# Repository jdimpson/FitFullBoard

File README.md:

FitFullBoard is a Raspberry Pi- and Raspberry Pi Zero-compatible daughter board intended to power up and power down the the RPi board in sync with outside signals. 

I use it to keep an RPi media player powered along with my television. I connect the fitfullboard's signal pin called EXTERNAL to a USB cable which I plug into my smart teevee (but I power the RPi from an independent power source.) When the teevee comes on, it brings its USB port on, which wakes up the RPi. When the teevee goes off, it brings its USB port down, which puts the RPi to sleep (following a configurable grace period).  It is possible to turn the teevee back on at just the wrong time so as to get them out of sync (after the grace period expires, while the RPi operating system is still shutting down). 

Python software is available in the [RPiIoT](https://github.com/jdimpson/RPiIoT) repo.

FitFullBoard uses an ATtiny85 to control power up / power down and to monitor the EXTERNAL signal, and python code running in the RPi to handle shutdown and grace period. The grace period works because the ATtiny will hold the shutdown signal to the RPI down indefinitely. If the EXTERNAL signal comes back on, the ATtiny with bring the shutdown signal back high again. If this happens within the grace period, the python software will not initiate shutdown. You can instead use the Linux kernel's builtin signal handling for shutdown, althuogh AFAIK it has no way of offering a grace period.

Raspberry Pi Pins used:
- GPIO3/Phys5/SCL is used to power up the RPi. This only works if the RPi has been shut down via the "poweroff" or "shutdown" Linux commands. THe board itself must still have power.
- GPIO17/Phy11 is connected to a momentary / tactile switch. Available for arbitrary software control (typically running my powerboard.py and associated code).
- GPIO27/Phy13 is connected to a resistor and then an LED. Available for arbitrary software control (e.g. flashing to show grace period, and typically running my powerboard.py and associated code).
- GPIO26/Phy37 is connected via transistor and appropriate hold up resistor to the LBO/Shutdown pin of the ATtiny85. This is how the Raspberry Pi knows to shut down. This is labelled LBO and referred to as "Low Battery" in the schematic because the circuit and my python lowbattery code were reused from the PowerBoard (https://github.com/jdimpson/PowerBoard) and PowerHolder (https://github.com/jdimpson/PowerHolder) projects, in which when the Li Ion battery level fell below 3.4VDC (or whatever) the boards sent an LBO signal to the raspberry pi to shutdown, again with a grace period that allowed you to maybe plug it into external power (typically running my powerboard.py and associated code).

ATtiny85 pin used:
- PB0/MOSI used as RX for soft UART (for debugging, note the arduino code doesn't RX currently)
- PB1/MISO used as TX for soft UART (for debugging)
- PB2/SCK used to send the LBO/shutdown signal that tells the RPi to power off following a grace period.
- PB3 used to receive EXTERNAL signal (e.g. teevee power on indication). Circuit can be held up to 5VDC or down to ground, depending on which pads you put the resistor on (DON'T ATTACH BOTH R4 and R5 RESISTORS).
- PB4 is attached to a momentary / tactile button to allow manual start of the RPi independent of the EXTernal signal.

Other items of Note:
- I honestly don't remember why I called this the FitFullBoard. Something about the phrase "sleeping in fits and starts" being an analogue to automatically starting up and shutting down in response to an external influence. But honestly who knows? At one point I called it GraceFullBoard because it allowed for graceful shutdown of a raspberry pi in response to a signal. I should have kept that name.
- ATtiny85 code works with Arduino IDE and requires the https://github.com/SpenceKonde/ATTinyCore library.
- Python code referenced above will be posted and linked to soon.
- The use of GPIO3 to cause a shutdown RPi to restart does not seem to be well known. At least, it's not referenced on pinout.xyz (https://pinout.xyz/pinout/pin5_gpio3#). I've personally tested it to work on RPi Zero Ws, RPi 3B, and an RPi 4B with updated firmware. Note that this behaviour of GPIO3 is *different* from that of the RUN pin that is found in elsewhere on the board (not on the 40-pin header). The RUN pin will, when brought high, cause the RPi to reboot, even if the CPU is already running. This crashes the OS, which isn't something I want to do regularly. GPIO3 acts like any other pin when the CPU is running normally. It only seems to have special behaviour when the the CPU has halted following a graceful shutdown of the OS. When it gets brought high, it will cause a reboot. But *only* when the CPU was halted. See also https://www.raspberrypi.org/forums/viewtopic.php?t=113200 and https://www.raspberrypi.org/forums/viewtopic.php?p=767687#p767687

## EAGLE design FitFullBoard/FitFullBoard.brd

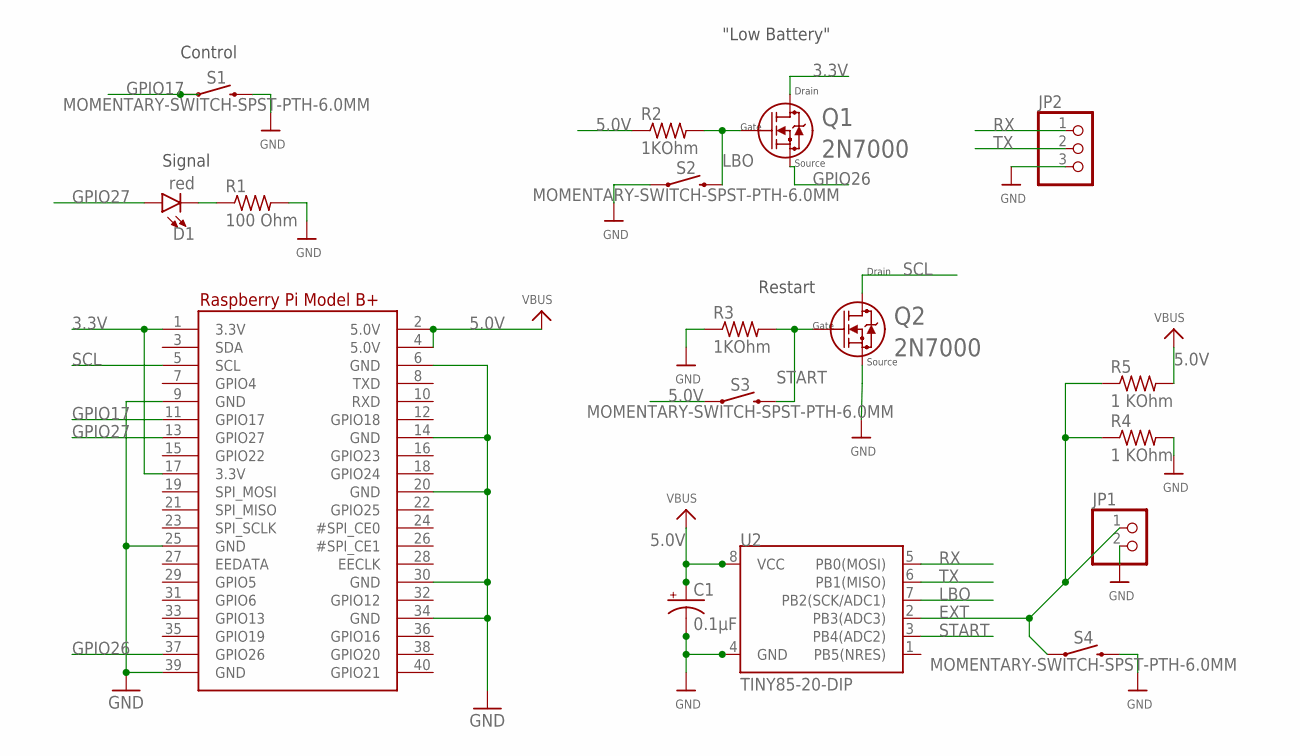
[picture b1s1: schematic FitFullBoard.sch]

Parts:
C1: 0.1µF; E2,5RE
D1: red; LED_5MM
JP1: HEADER-1X2; 1X02_OVAL
JP2: PINHD-1X3CB; 1X03-CLEANBIG
Q1, Q2: 2N7000; TO-92
R1: 100 Ohm; 0805-THM
R2, R3: 1KOhm; 0805-THM
R4, R5: 1 KOhm; 0805-THM
RPI1: RASPBERRYPI_BPLUS_BONNETNODIM; PI_BONNET_NODIM
S1, S2, S3, S4: MOMENTARY-SWITCH-SPST-PTH-6.0MM; TACTILE_SWITCH_PTH_6.0MM
U2: TINY85-20-DIP; DIP08_MCU

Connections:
3.3V: Q1.3 (2), RPI1.1 (3.3V), RPI1.17 (3.3V)
5.0V: C1.+, R2.1, R5.2, RPI1.2 (5.0V), RPI1.4 (5.0V), S3.1, U2.8 (VCC)
EXT: JP1.1, R4.1, R5.1, S4.1, U2.2 (PB3(ADC3))
GND: C1.-, JP1.2, JP2.3, Q2.1 (3), R1.2, R3.1, R4.2, RPI1.6 (GND), RPI1.9 (GND), RPI1.14 (GND), RPI1.20 (GND), RPI1.25 (GND), RPI1.30 (GND), RPI1.34 (GND), RPI1.39 (GND), S1.3 (2), S2.1, S4.3 (2), U2.4 (GND)
GPIO17: RPI1.11 (GPIO17), S1.1
GPIO26: Q1.1 (3), RPI1.37 (GPIO26)
GPIO27: D1.A, RPI1.13 (GPIO27)
LBO: Q1.2 (1), R2.2, S2.3 (2), U2.7 (PB2(SCK/ADC1))
unnamed: D1.K (C), R1.1
RX: JP2.1, U2.5 (PB0(MOSI))
SCL: Q2.3 (2), RPI1.5 (SCL)
START: Q2.2 (1), R3.2, S3.3 (2), U2.3 (PB4(ADC2))
TX: JP2.2, U2.6 (PB1(MISO))

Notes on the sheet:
Signal
Control
Source
Gate
"Low Battery"
Drain
Restart

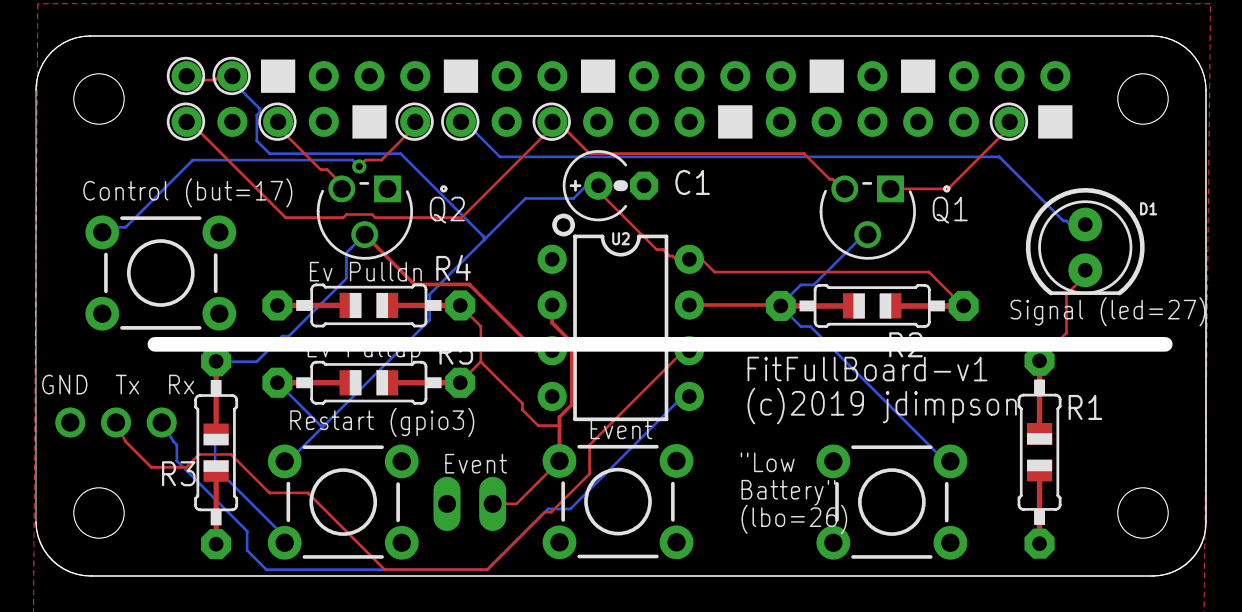
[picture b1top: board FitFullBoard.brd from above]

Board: 2 copper layers, 64.2 x 29.2 mm, 17 parts (0 on the bottom side), 13 nets.

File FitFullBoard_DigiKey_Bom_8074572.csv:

"Manufacturer Part Number","Manufacturer","Digi-Key Part Number","Customer Reference","Reference Designator","Packaging","Part Status","Quantity","Unit Price","Extended Price","Quantity Available","Mfg Std Lead Time","Description","RoHS Status","Lead Free Status","REACH Status"
"ATTINY85-20PU","Microchip Technology","ATTINY85-20PU-ND","U2","","Tube","Active","1","1.20000","$1.20","144","21 Weeks","IC MCU 8BIT 8KB FLASH 8DIP","ROHS3 Compliant","Lead free","REACH Unaffected"
"USP1H0R1MDD","Nichicon","493-15992-ND","C1","","Bulk","Active","1","0.35000","$0.35","2591","15 Weeks","CAP ALUM 0.1UF 20% 50V RADIAL","ROHS3 Compliant","Lead free","REACH Unaffected"
"SFR2500001001FR500","Vishay Beyschlag/Draloric/BC Components","PPC1.00KYCT-ND","R2,R3,R4/5","","Cut Tape (CT)","Active","3","0.14000","$0.42","23724","22 Weeks","RES 1K OHM 0.4W 1% AXIAL","ROHS3 Compliant","Lead free","Not Available"
"SFR2500001000FR500","Vishay Beyschlag/Draloric/BC Components","PPC100YCT-ND","R1","","Cut Tape (CT)","Active","1","0.14000","$0.14","13597","22 Weeks","RES 100 OHM 0.4W 1% AXIAL","ROHS3 Compliant","Lead free","Not Available"
"2N7000-G","Microchip Technology","2N7000-G-ND","Q1,Q2","","Bag","Active","2","0.37000","$0.74","2054","21 Weeks","MOSFET N-CH 60V 0.2A TO92-3","ROHS3 Compliant","Lead free","REACH Unaffected"
"C503B-RAN-CZ0C0AA1","Cree Inc.","C503B-RAN-CZ0C0AA1-ND","D1","","Bulk","Active","1","0.15000","$0.15","51470","4 Weeks","LED RED CLEAR 5MM ROUND T/H","RoHS Compliant","Lead free","Not Available"

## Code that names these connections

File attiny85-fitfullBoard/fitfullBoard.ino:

/**********************************************************************
 * ATTiny85 MCU monitors an external signal. When the signal (EXT) 
 * activates, MCU will bring RPi GPIO3 (START) low, which, if the RPi 
 * previously did a poweroff, will cause it to restart. At the same time, 
 * MCU will bring RPi GPIO26 (LBO) high. When the EXT signal deactivates, 
 * MCU will bring RPi GPIO26 (LBO) low.
 * 
 * The intention for the signal on GPIO26 is that the RPi runs software 
 * that treats it as a low-battery signal. When the software starts up, 
 * it looks at GPIO26. If high, it knows to use the pin as low-battery signal. 
 * (If low, don't monitor pin.) When GPIO26 goes low, RPi software will 
 * initiate a graceful shutdown.
 * 
 * Could probably do both the restart and LBO on GPIO3, but GPIO26 is used
 * for LBO due to commonality with my batter power boards.
 * 
 * Don't forget to level shift the LBO and START pins, assuming MCU is running 
 * at 5V.
 * 
 * (c) 2019 jdimpson
 **********************************************************************/

// NOTE: right now, the EXT signal must be HIGH for on, LOW for off. Would 
// be cool to use EEPROM to store the EXT signal mode, and adjust accordingly.

#include <SoftwareSerial.h>
#include <EEPROM.h>
#include "Debounce.h"

#define EXT   3 // Physical 2 / PB3 / A3
#define START 4 // Physical 3 / PB4
#define RX   -1 // Physical 5 / PB0; Reserved, not currently used. 
#define TX    1 // Physical 6 / PB1
#define LBO   2 // Physical 7 / PB2

#define OFF          0
#define STARTUP      1
#define SYNC_SIGNAL  2
#define HIGH_MONITOR 3
#define LOW_MONITOR  4

SoftwareSerial ss(RX, TX);
Debounce Button(EXT);

int state = STARTUP;
int prevstate = OFF;

void setup() {
  ss.begin(9600);
  ss.println(F("fitfullBoard"));
  ss.println(F(__FILE__));
  ss.print(F("compiled ")); 
  ss.println(__DATE__);
  delay(10);

  pinMode(EXT,INPUT);
  pinMode(LBO,OUTPUT);
  pinMode(START,INPUT); // leave high impedence

  ss.println("Waiting a second...");
  delay(1000);
  ss.println("Go!");
}

void loop() {
  state_machine(); 
}

inline void stay_awake() {
  if(digitalRead(LBO) != HIGH) {
    digitalWrite(LBO,HIGH);
  }
}

inline void wake_up() {
  pinMode(START,OUTPUT); // go low impedence
  digitalWrite(START,HIGH); // then go to high, which will switch the RPi's GPIO3 to ground via MOSFET
  delay(1000);
  pinMode(START,INPUT);// return to high impedence
}

inline void stay_sleep() {
  if(digitalRead(LBO) == HIGH) {
    digitalWrite(LBO,LOW);
  }
}

inline void stahp() {
  abort();
  // or assert(0); #include <assert.h> 
  // or set_sleep_mode(SLEEP_MODE_PWN_DOWN); cli(); sleep_mode(); #include <avr/sleep.h>
}

inline void state_machine() {
  bool delta = false;
  bool extsig = Button.read();

  if(state != prevstate) {
    delta = true;
    ss.print(prevstate);
    ss.print(F(" changed to "));
    ss.println(state);
    delay(50);
  }
  prevstate = state;
  //ss.print(F("extsig "));
  //ss.println(extsig);

  switch(state) {
    case STARTUP:
      state = SYNC_SIGNAL;
      stay_awake();
      break;

    case SYNC_SIGNAL:
      stay_awake();
      if(extsig) {
        state = HIGH_MONITOR;
      }
      break;

    case HIGH_MONITOR:
      if(delta) {
        wake_up();
      }
      stay_awake();
      if(!extsig) {
        state = LOW_MONITOR;
      }
      break;

    case LOW_MONITOR:
      stay_sleep();
      if(extsig) {
        state = HIGH_MONITOR;
      }
      break;

    default:
      ss.print("UNKNOWN STATE, ABORTING ");
      ss.println(state);
      delay(50);
      stahp();
      break;
  }

  delay(100);
}

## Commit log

2020-09-07 Created
2020-09-07 Implementation details
2020-09-07 Added forgotten ATtiny pin PB4 description
2020-09-07 added arduino code
2020-09-07 Gerber files used to make some boards
2020-09-07 Bill of Materials from DigiKey
2020-09-08 Blathering about GPIO3
2020-09-08 more outgassing
2020-09-08 I should proofread before committing
2020-09-09 link to python repo
2020-09-09 picture of board
2020-09-09 link to picture

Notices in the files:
parts and their libraries:
microbuilder: This work is placed in the public domain, and may be freely used for commercial and non-commercial work with the following conditions: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
SparkFun-LED: Licensing: Creative Commons ShareAlike 4.0 International - https://creativecommons.org/licenses/by-sa/4.0
